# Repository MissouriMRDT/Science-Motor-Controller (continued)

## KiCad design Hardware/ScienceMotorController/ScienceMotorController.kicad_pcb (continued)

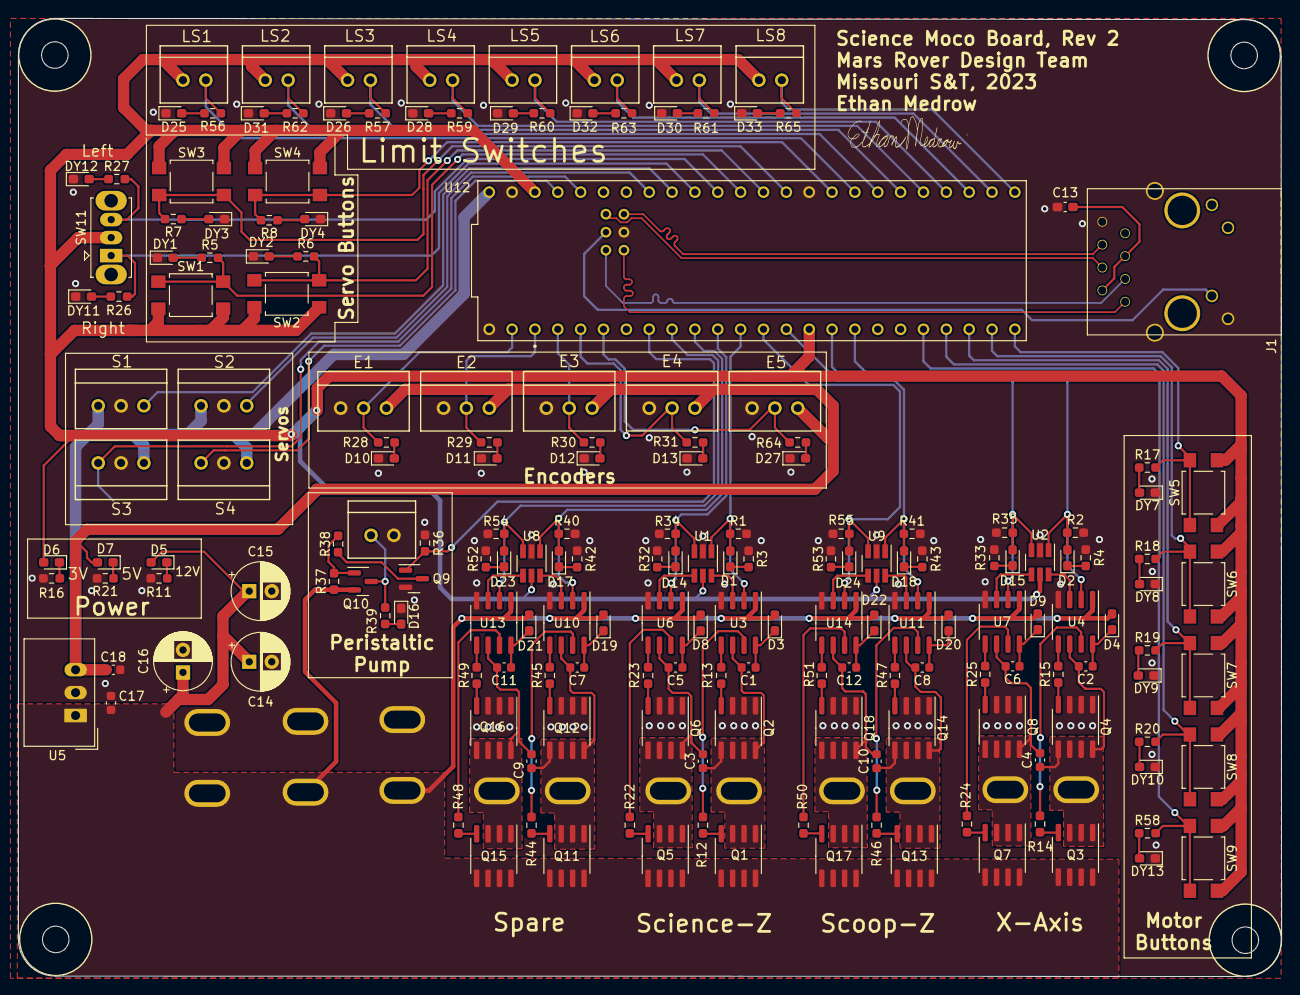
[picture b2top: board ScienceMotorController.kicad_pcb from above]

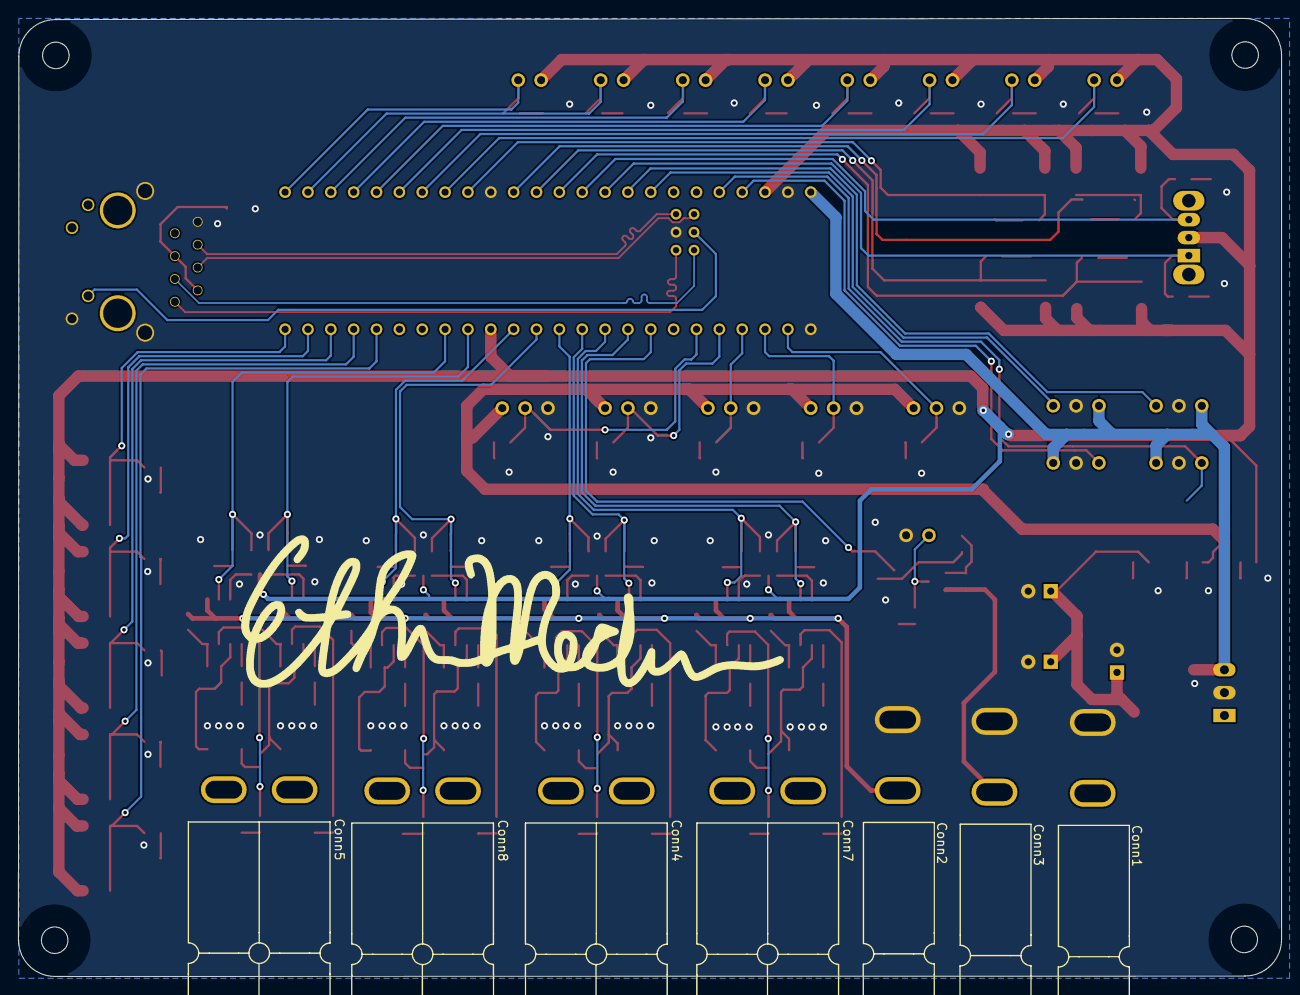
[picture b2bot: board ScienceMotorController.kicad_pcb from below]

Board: 2 copper layers, 140.4 x 106.5 mm, 197 parts (7 on the bottom side), 142 nets.

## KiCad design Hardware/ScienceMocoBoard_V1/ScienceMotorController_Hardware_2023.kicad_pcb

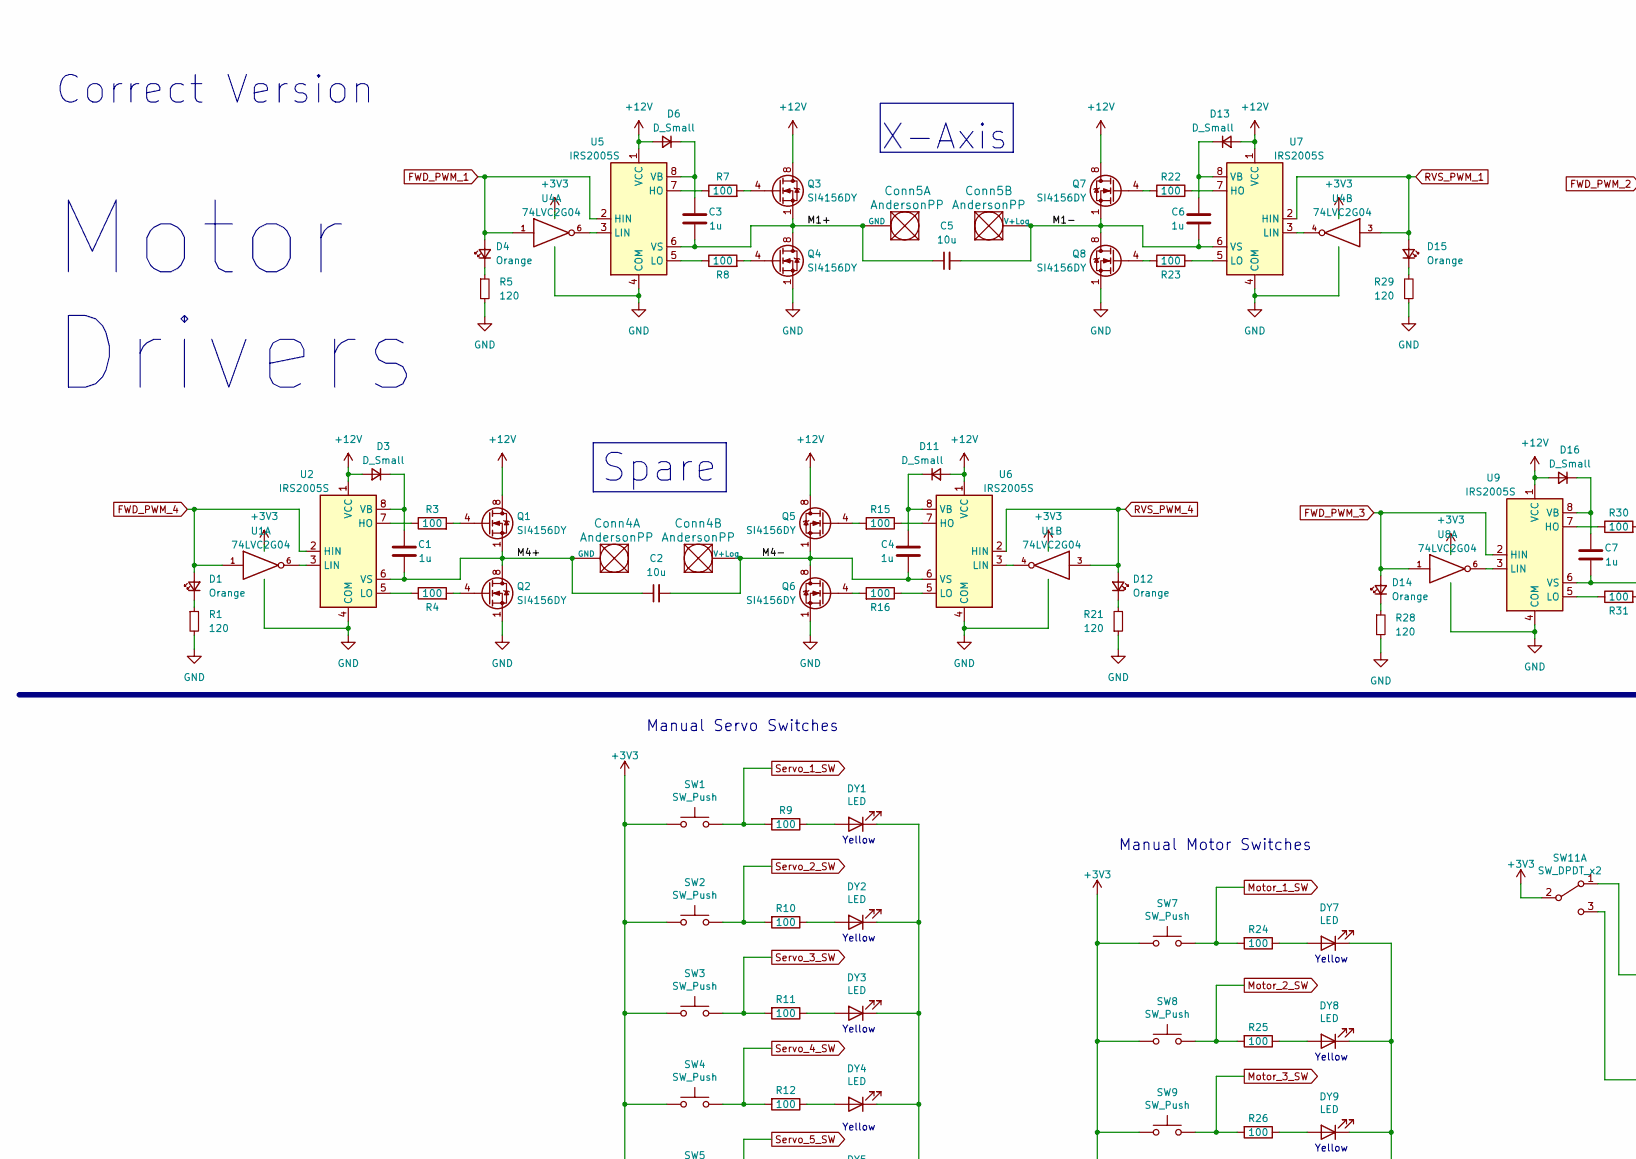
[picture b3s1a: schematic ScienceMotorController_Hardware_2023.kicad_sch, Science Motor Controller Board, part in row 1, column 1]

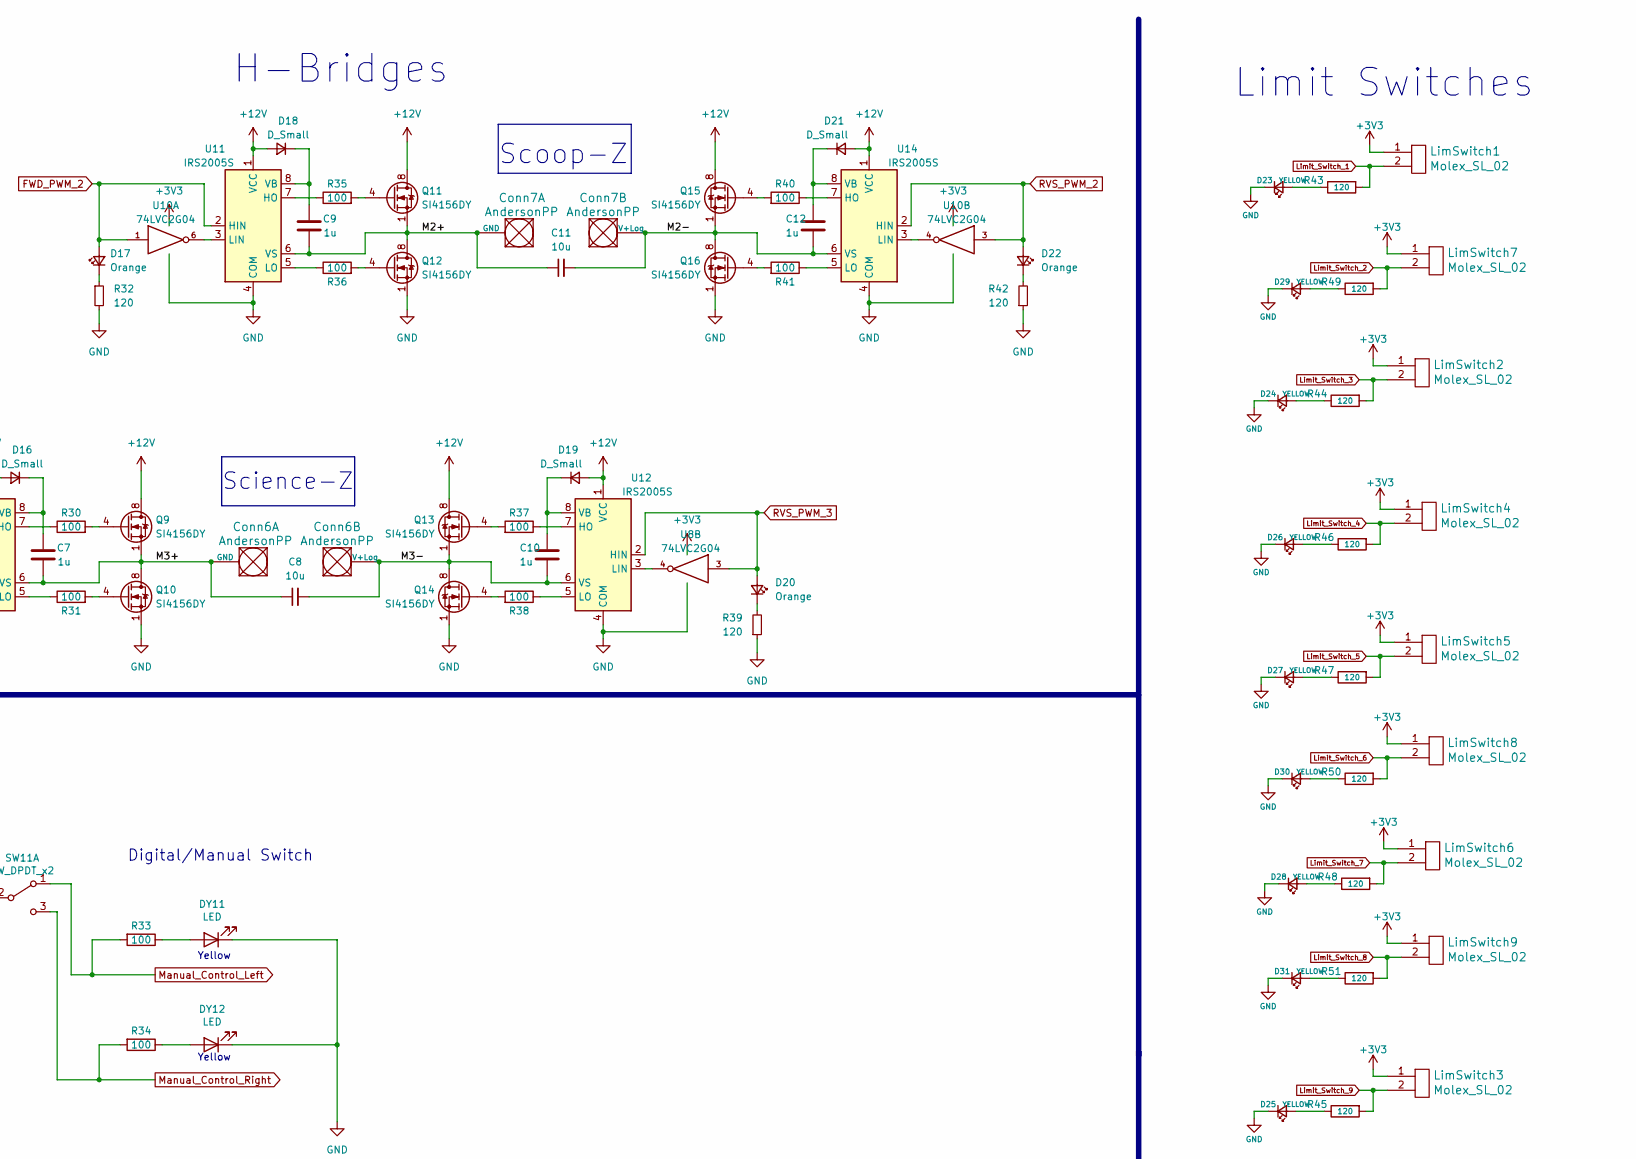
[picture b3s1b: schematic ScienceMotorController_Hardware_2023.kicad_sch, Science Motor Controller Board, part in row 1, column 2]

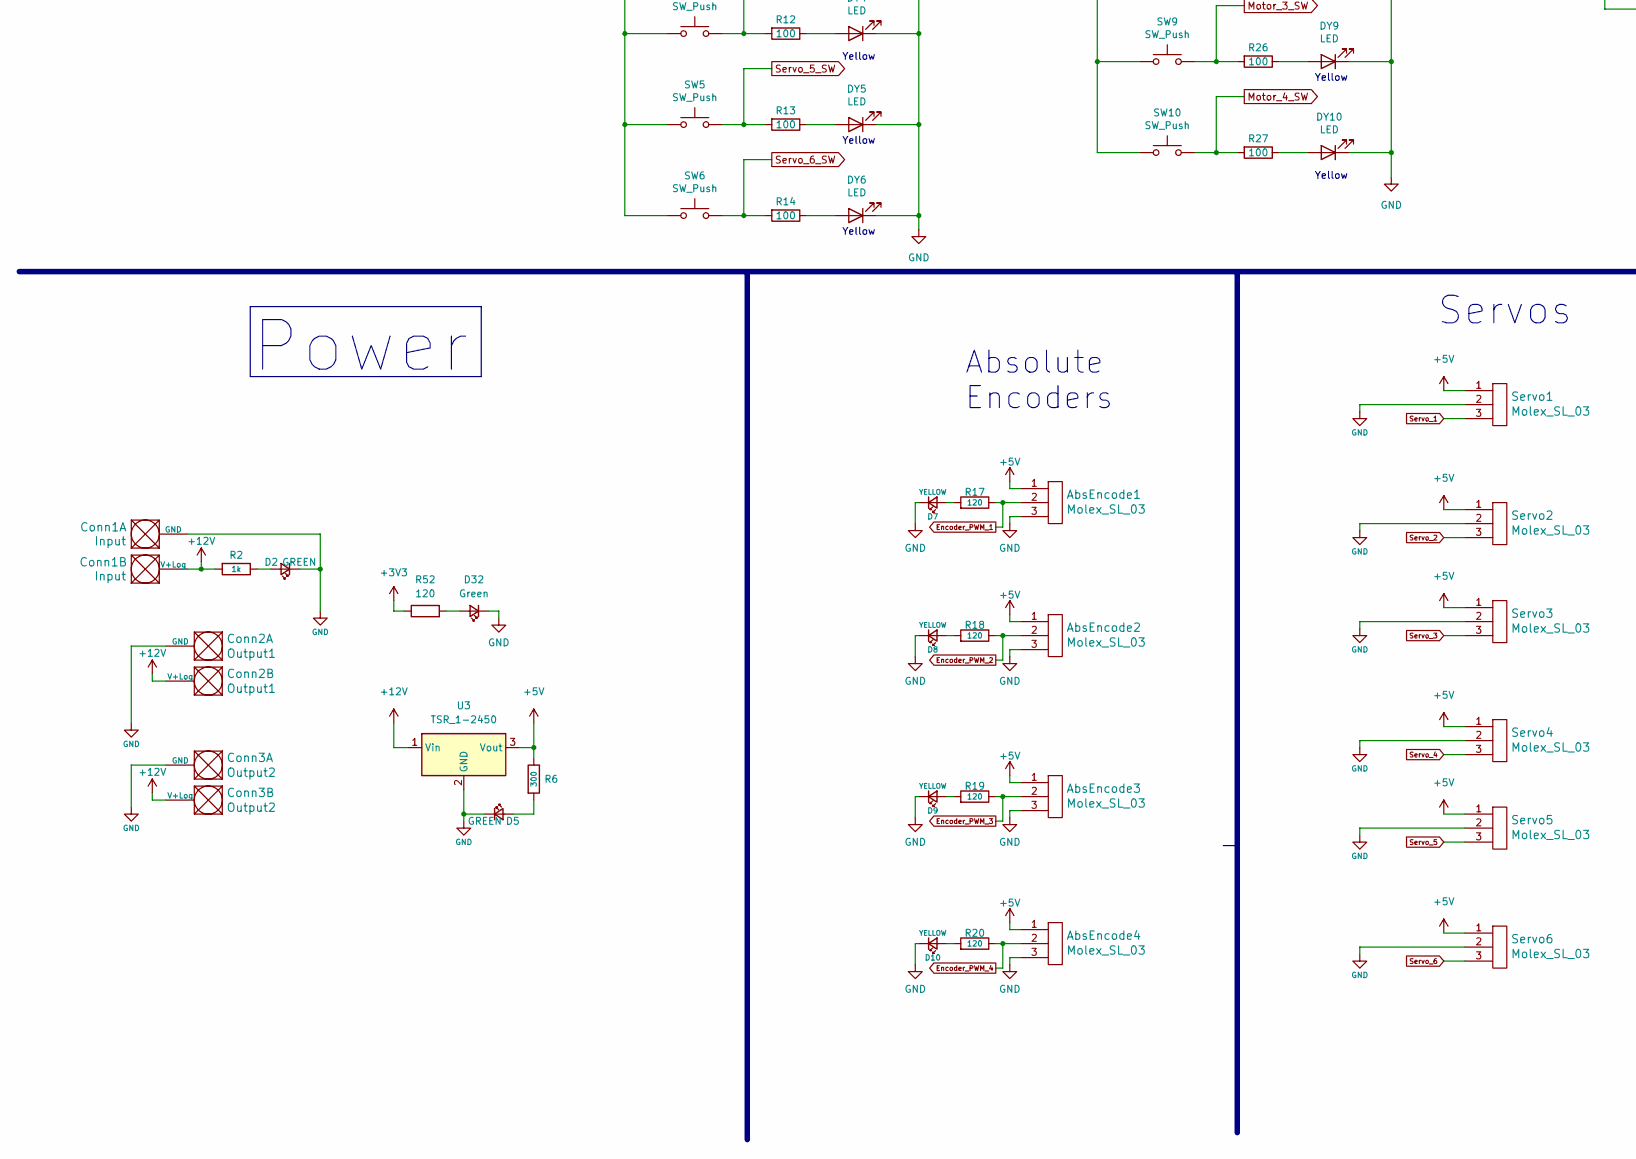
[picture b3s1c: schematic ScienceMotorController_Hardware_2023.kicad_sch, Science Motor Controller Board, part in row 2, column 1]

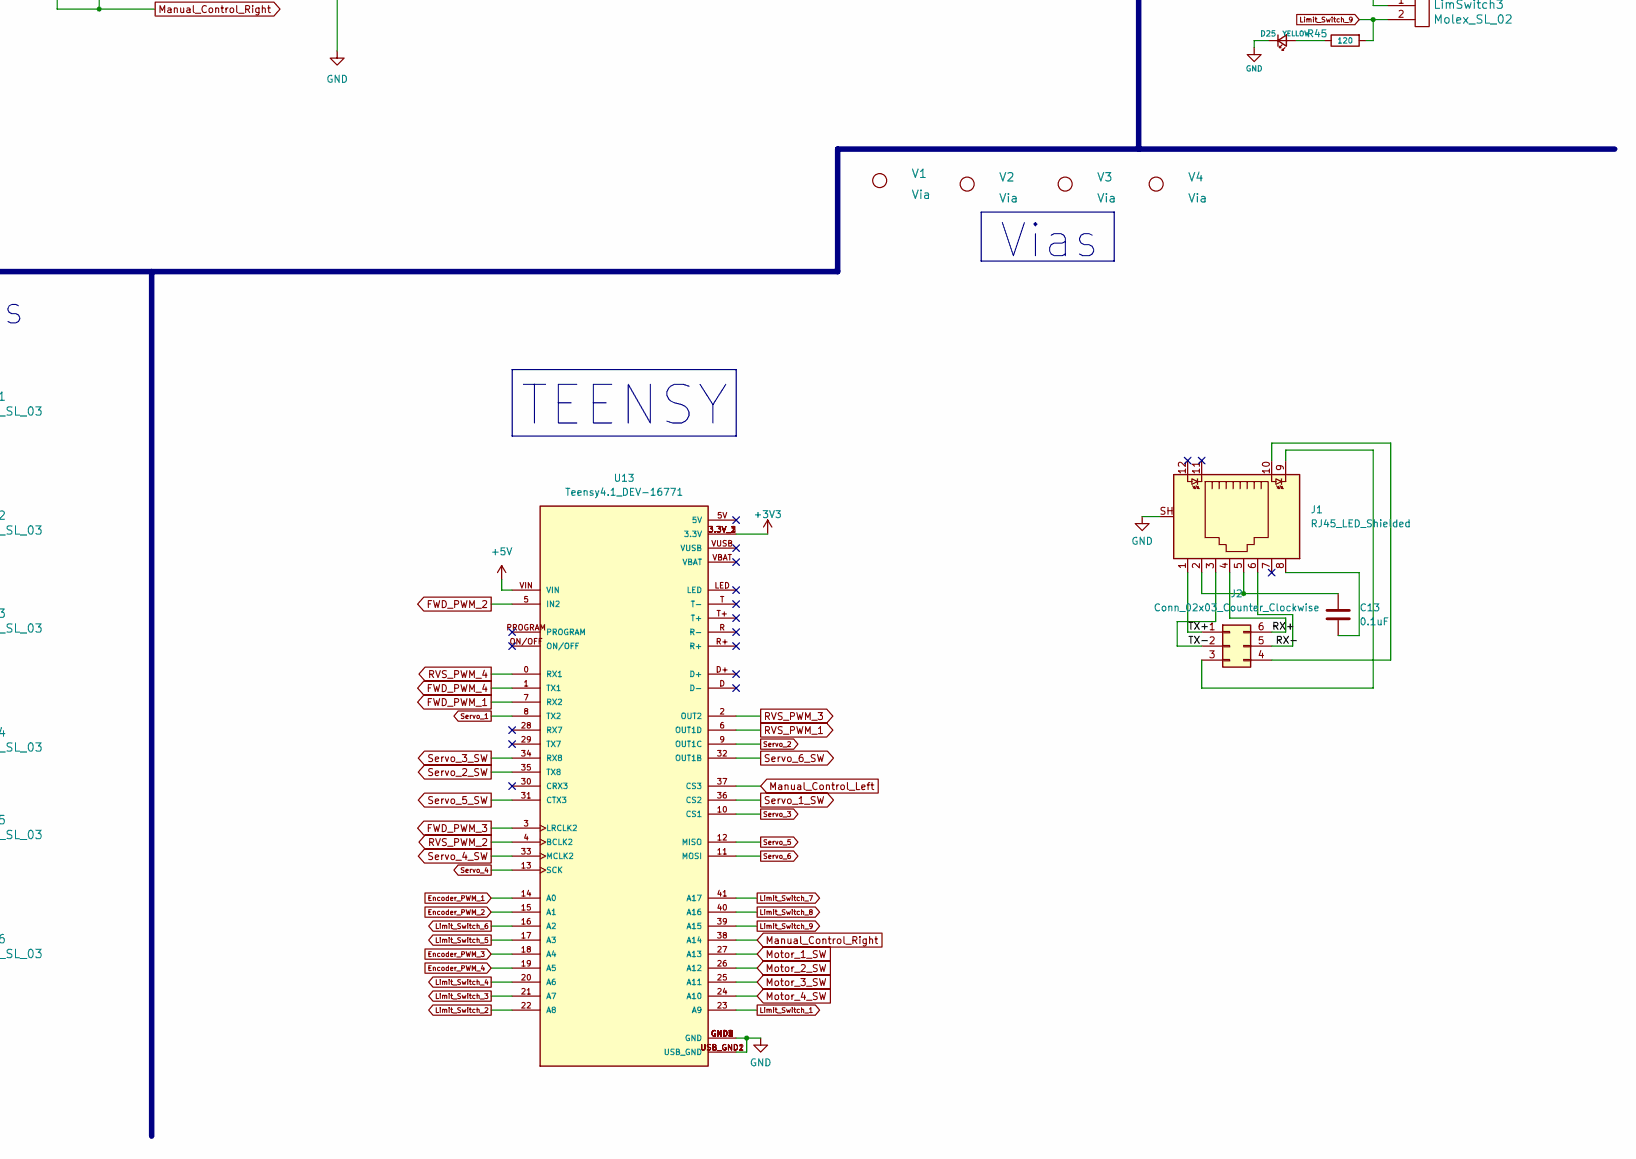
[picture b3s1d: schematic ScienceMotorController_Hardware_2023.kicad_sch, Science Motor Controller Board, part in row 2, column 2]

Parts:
AbsEncode1, AbsEncode2, AbsEncode3, AbsEncode4: Molex_SL_03; MOLEX_SL_03_Vertical
C1, C3, C4, C6, C7, C9, C10, C12: 1u; C_0603_1608Metric
C2, C5, C8, C11: 10u; C_0603_1608Metric
C13: 0.1uF; C_0603_1608Metric_Pad1.08x0.95mm_HandSolder
Conn1: Input; Square_Anderson_2_H_Side_By_Side
Conn2: Output1; Square_Anderson_2_H_Side_By_Side
Conn3: Output2; Square_Anderson_2_H_Side_By_Side
Conn4, Conn5, Conn6, Conn7: AndersonPP; Square_Anderson_2_H_Side_By_Side
D1, D4, D12, D14, D15, D17, D20, D22: Orange; LED_0603_1608Metric_Pad1.05x0.95mm_HandSolder
D2, D5: GREEN; LED_0603_1608Metric_Pad1.05x0.95mm_HandSolder
D3, D6, D11, D13, D16, D18, D19, D21: D_Small; LED_0603_1608Metric_Pad1.05x0.95mm_HandSolder
D7, D8, D9, D10, D23, D24, D25, D26, D27, D28, D29, D30, D31: YELLOW; LED_0603_1608Metric_Pad1.05x0.95mm_HandSolder
D32: Green; LED_0603_1608Metric_Pad1.05x0.95mm_HandSolder
DY1, DY2, DY3, DY4, DY5, DY6, DY7, DY8, DY9, DY10, DY11, DY12: LED; LED_0603_1608Metric_Pad1.05x0.95mm_HandSolder
J1: RJ45_LED_Shielded; RJ45_Teensy
J2: Conn_02x03_Counter_Clockwise; PinHeader_2x03_P2.00mm_Vertical
LimSwitch1, LimSwitch2, LimSwitch3, LimSwitch4, LimSwitch5, LimSwitch6, LimSwitch7, LimSwitch8, LimSwitch9: Molex_SL_02; MOLEX_SL_02_Vertical
Q1, Q2, Q3, Q4, Q5, Q6, Q7, Q8, Q9, Q10, Q11, Q12, Q13, Q14, Q15, Q16: SI4156DY; SOIC-8_3.9x4.9mm_P1.27mm
R1, R5, R17, R18, R19, R20, R21, R28, R29, R32, R39, R42, R43, R44, R45, R46, R47, R48, R49, R50, R51, R52: 120; R_0603_1608Metric_Pad0.98x0.95mm_HandSolder
R2: 1k; R_0603_1608Metric_Pad0.98x0.95mm_HandSolder
R3, R4, R7, R8, R9, R10, R11, R12, R13, R14, R15, R16, R22, R23, R24, R25, R26, R27, R30, R31, R33, R34, R35, R36, R37, R38, R40, R41: 100; R_0603_1608Metric_Pad0.98x0.95mm_HandSolder
R6: 300; R_0603_1608Metric_Pad0.98x0.95mm_HandSolder
SW1, SW2, SW3, SW4, SW5, SW6, SW7, SW8, SW9, SW10: SW_Push; SW_SPST_EVPBF
SW11: SW_DPDT_x2; SW_Slide_1P2T_CK_OS102011MS2Q
Servo1, Servo2, Servo3, Servo4, Servo5, Servo6: Molex_SL_03; MOLEX_SL_03_Vertical
U1, U4, U8, U10: 74LVC2G04; SOT-23-6_Handsoldering
U2, U5, U6, U7, U9, U11, U12, U14: IRS2005S; SOIC-8_3.9x4.9mm_P1.27mm
U3: TSR_1-2450; Converter_DCDC_TRACO_TSR-1_THT
U13: Teensy4.1_DEV-16771; Teensy_4_1_Bare; PARTREV 4.1
V1, V2, V3, V4: Via; 4_40_Hole_Corner

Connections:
+3V3: LimSwitch1.1, LimSwitch2.1, LimSwitch3.1, LimSwitch4.1, LimSwitch5.1, LimSwitch6.1, LimSwitch7.1, LimSwitch8.1, LimSwitch9.1, R52.1, SW1.2, SW2.1, SW3.1, SW4.1, SW5.1, SW6.1, SW7.2, SW8.1, SW9.1, SW10.1, SW11.2 (B), U1.5 (VCC), U4.5 (VCC), U8.5 (VCC), U10.5 (VCC), U13.3.3V_1 (3.3V), U13.3.3V_2 (3.3V), U13.3.3V_3 (3.3V)
+5V: AbsEncode1.1, AbsEncode2.1, AbsEncode3.1, AbsEncode4.1, R6.1, Servo1.1, Servo2.1, Servo3.1, Servo4.1, Servo5.1, Servo6.1, U3.3 (Vout), U13.VIN
+12V: Conn1.2 (V+Log), Conn2.2 (V+Log), Conn3.2 (V+Log), D3.2 (A), D6.2 (A), D11.2 (A), D13.2 (A), D16.2 (A), D18.2 (A), D19.2 (A), D21.2 (A), Q1.5 (D), Q1.6 (D), Q1.7 (D), Q1.8 (D), Q3.5 (D), Q3.6 (D), Q3.7 (D), Q3.8 (D), Q5.5 (D), Q5.6 (D), Q5.7 (D), Q5.8 (D), Q7.5 (D), Q7.6 (D), Q7.7 (D), Q7.8 (D), Q9.5 (D), Q9.6 (D), Q9.7 (D), Q9.8 (D), Q11.5 (D), Q11.6 (D), Q11.7 (D), Q11.8 (D), Q13.5 (D), Q13.6 (D), Q13.7 (D), Q13.8 (D), Q15.5 (D), Q15.6 (D), Q15.7 (D), Q15.8 (D), R2.2, U2.1 (VCC), U3.1 (Vin), U5.1 (VCC), U6.1 (VCC), U7.1 (VCC), U9.1 (VCC), U11.1 (VCC), U12.1 (VCC), U14.1 (VCC)
/M1+: C3.2, C5.1, Conn5.1 (GND), Q3.1 (S), Q3.2 (S), Q3.3 (S), Q4.5 (D), Q4.6 (D), Q4.7 (D), Q4.8 (D), U5.6 (VS)
/M1-: C5.2, C6.2, Conn5.2 (V+Log), Q7.1 (S), Q7.2 (S), Q7.3 (S), Q8.5 (D), Q8.6 (D), Q8.7 (D), Q8.8 (D), U7.6 (VS)
/M2+: C9.2, C11.1, Conn7.1 (GND), Q11.1 (S), Q11.2 (S), Q11.3 (S), Q12.5 (D), Q12.6 (D), Q12.7 (D), Q12.8 (D), U11.6 (VS)
/M2-: C11.2, C12.2, Conn7.2 (V+Log), Q15.1 (S), Q15.2 (S), Q15.3 (S), Q16.5 (D), Q16.6 (D), Q16.7 (D), Q16.8 (D), U14.6 (VS)
/M3+: C7.2, C8.1, Conn6.1 (GND), Q9.1 (S), Q9.2 (S), Q9.3 (S), Q10.5 (D), Q10.6 (D), Q10.7 (D), Q10.8 (D), U9.6 (VS)
/M3-: C8.2, C10.2, Conn6.2 (V+Log), Q13.1 (S), Q13.2 (S), Q13.3 (S), Q14.5 (D), Q14.6 (D), Q14.7 (D), Q14.8 (D), U12.6 (VS)
/M4+: C1.2, C2.1, Conn4.1 (GND), Q1.1 (S), Q1.2 (S), Q1.3 (S), Q2.5 (D), Q2.6 (D), Q2.7 (D), Q2.8 (D), U2.6 (VS)
/M4-: C2.2, C4.2, Conn4.2 (V+Log), Q5.1 (S), Q5.2 (S), Q5.3 (S), Q6.5 (D), Q6.6 (D), Q6.7 (D), Q6.8 (D), U6.6 (VS)
/RX+: J1.4, J2.6
/RX-: J1.6, J2.5
/TX+: J1.1, J2.1
/TX-: J1.3, J2.2
Encoder_PWM_1: AbsEncode1.2, R17.1, U13.14 (A0)
Encoder_PWM_2: AbsEncode2.2, R18.1, U13.15 (A1)
Encoder_PWM_3: AbsEncode3.2, R19.1, U13.18 (A4)
Encoder_PWM_4: AbsEncode4.2, R20.1, U13.19 (A5)
FWD_PWM_1: D4.2 (A), U4.1, U5.2 (HIN), U13.7 (RX2)
FWD_PWM_2: D17.2 (A), U10.1, U11.2 (HIN), U13.5 (IN2)
FWD_PWM_3: D14.2 (A), U8.1, U9.2 (HIN), U13.3 (LRCLK2)
FWD_PWM_4: D1.2 (A), U1.1, U2.2 (HIN), U13.1 (TX1)
GND: AbsEncode1.3, AbsEncode2.3, AbsEncode3.3, AbsEncode4.3, Conn1.1 (GND), Conn2.1 (GND), Conn3.1 (GND), D2.1 (K), D5.1 (K), D7.1 (K), D8.1 (K), D9.1 (K), D10.1 (K), D23.1 (K), D24.1 (K), D25.1 (K), D26.1 (K), D27.1 (K), D28.1 (K), D29.1 (K), D30.1 (K), D31.1 (K), D32.1 (K), DY1.1 (K), DY2.1 (K), DY3.1 (K), DY4.1 (K), DY5.1 (K), DY6.1 (K), DY7.1 (K), DY8.1 (K), DY9.1 (K), DY10.1 (K), DY11.1 (K), DY12.1 (K), J1.SH, Q2.1 (S), Q2.2 (S), Q2.3 (S), Q4.1 (S), Q4.2 (S), Q4.3 (S), Q6.1 (S), Q6.2 (S), Q6.3 (S), Q8.1 (S), Q8.2 (S), Q8.3 (S), Q10.1 (S), Q10.2 (S), Q10.3 (S), Q12.1 (S), Q12.2 (S), Q12.3 (S), Q14.1 (S), Q14.2 (S), Q14.3 (S), Q16.1 (S), Q16.2 (S), Q16.3 (S), R1.2, R5.2, R21.1, R28.2, R29.1, R32.2, R39.1, R42.1, Servo1.2, Servo2.2, Servo3.2, Servo4.2, Servo5.2, Servo6.2, U1.2 (GND), U2.4 (COM), U3.2 (GND), U4.2 (GND), U5.4 (COM), U6.4 (COM), U7.4 (COM), U8.2 (GND), U9.4 (COM), U10.2 (GND), U11.4 (COM), U12.4 (COM), U13.GND1 (GND), U13.GND2 (GND), U13.GND3 (GND), U13.GND4 (GND), U13.GND5 (GND), U13.USB_GND1 (USB_GND), U13.USB_GND2 (USB_GND), U14.4 (COM)
Limit_Switch_1: LimSwitch1.2, R43.2, U13.23 (A9)
Limit_Switch_2: LimSwitch7.2, R49.2, U13.22 (A8)
Limit_Switch_3: LimSwitch2.2, R44.2, U13.21 (A7)
Limit_Switch_4: LimSwitch4.2, R46.2, U13.20 (A6)
Limit_Switch_5: LimSwitch5.2, R47.2, U13.17 (A3)
Limit_Switch_6: LimSwitch8.2, R50.2, U13.16 (A2)
Limit_Switch_7: LimSwitch6.2, R48.2, U13.41 (A17)
Limit_Switch_8: LimSwitch9.2, R51.2, U13.40 (A16)
Limit_Switch_9: LimSwitch3.2, R45.2, U13.39 (A15)
Manual_Control_Left: R33.2, SW11.1 (A), U13.37 (CS3)
Manual_Control_Right: R34.2, SW11.3 (C), U13.38 (A14)
Motor_1_SW: R24.2, SW7.1, U13.27 (A13)
Motor_2_SW: R25.2, SW8.2, U13.26 (A12)
Motor_3_SW: R26.2, SW9.2, U13.25 (A11)
Motor_4_SW: R27.2, SW10.2, U13.24 (A10)
unnamed: C1.1, D3.1 (K), U2.8 (VB)
unnamed: C3.1, D6.1 (K), U5.8 (VB)
unnamed: C4.1, D11.1 (K), U6.8 (VB)
unnamed: C6.1, D13.1 (K), U7.8 (VB)
unnamed: C7.1, D16.1 (K), U9.8 (VB)
unnamed: C9.1, D18.1 (K), U11.8 (VB)
unnamed: C10.1, D19.1 (K), U12.8 (VB)
unnamed: C12.1, D21.1 (K), U14.8 (VB)
unnamed: C13.1, J1.2, J1.5
unnamed: C13.2, J1.8
unnamed: D1.1 (K), R1.1
unnamed: D2.2 (A), R2.1
unnamed: D4.1 (K), R5.1
unnamed: D5.2 (A), R6.2
unnamed: D7.2 (A), R17.2
unnamed: D8.2 (A), R18.2
unnamed: D9.2 (A), R19.2
unnamed: D10.2 (A), R20.2
unnamed: D12.1 (K), R21.2
unnamed: D14.1 (K), R28.1
unnamed: D15.1 (K), R29.2
unnamed: D17.1 (K), R32.1
unnamed: D20.1 (K), R39.2
unnamed: D22.1 (K), R42.2
unnamed: D23.2 (A), R43.1
unnamed: D24.2 (A), R44.1
unnamed: D25.2 (A), R45.1
unnamed: D26.2 (A), R46.1
unnamed: D27.2 (A), R47.1
unnamed: D28.2 (A), R48.1
unnamed: D29.2 (A), R49.1
unnamed: D30.2 (A), R50.1
unnamed: D31.2 (A), R51.1
unnamed: D32.2 (A), R52.2
unnamed: DY1.2 (A), R9.1
unnamed: DY2.2 (A), R10.1
unnamed: DY3.2 (A), R11.1
unnamed: DY4.2 (A), R12.1
unnamed: DY5.2 (A), R13.1
unnamed: DY6.2 (A), R14.1
unnamed: DY7.2 (A), R24.1
unnamed: DY8.2 (A), R25.1
unnamed: DY9.2 (A), R26.1
unnamed: DY10.2 (A), R27.1
unnamed: DY11.2 (A), R33.1
unnamed: DY12.2 (A), R34.1
unnamed: J1.9, J2.3
unnamed: J1.10, J2.4
unnamed: Q1.4 (G), R3.2
unnamed: Q2.4 (G), R4.2
unnamed: Q3.4 (G), R7.2
unnamed: Q4.4 (G), R8.2
unnamed: Q5.4 (G), R15.2
unnamed: Q6.4 (G), R16.2
unnamed: Q7.4 (G), R22.2
unnamed: Q8.4 (G), R23.2
unnamed: Q9.4 (G), R30.2
unnamed: Q10.4 (G), R31.2
unnamed: Q11.4 (G), R35.2
unnamed: Q12.4 (G), R36.2
unnamed: Q13.4 (G), R37.2
unnamed: Q14.4 (G), R38.2
unnamed: Q15.4 (G), R40.2
unnamed: Q16.4 (G), R41.2
unnamed: R3.1, U2.7 (HO)
unnamed: R4.1, U2.5 (LO)
unnamed: R7.1, U5.7 (HO)
unnamed: R8.1, U5.5 (LO)
unnamed: R15.1, U6.7 (HO)
unnamed: R16.1, U6.5 (LO)
unnamed: R22.1, U7.7 (HO)
unnamed: R23.1, U7.5 (LO)
unnamed: R30.1, U9.7 (HO)
unnamed: R31.1, U9.5 (LO)
unnamed: R35.1, U11.7 (HO)
unnamed: R36.1, U11.5 (LO)
unnamed: R37.1, U12.7 (HO)
unnamed: R38.1, U12.5 (LO)
unnamed: R40.1, U14.7 (HO)
unnamed: R41.1, U14.5 (LO)
unnamed: U1.4, U6.3 (LIN)
unnamed: U1.6, U2.3 (LIN)
unnamed: U4.4, U7.3 (LIN)
unnamed: U4.6, U5.3 (LIN)
unnamed: U8.6, U9.3 (LIN)
unnamed: U10.4, U14.3 (LIN)
unnamed: U10.6, U11.3 (LIN)
unnamed: U8.4, U12.3 (LIN)
RVS_PWM_1: D15.2 (A), U4.3, U7.2 (HIN), U13.6 (OUT1D)
RVS_PWM_2: D22.2 (A), U10.3, U13.4 (BCLK2), U14.2 (HIN)
RVS_PWM_3: D20.2 (A), U8.3, U12.2 (HIN), U13.2 (OUT2)
RVS_PWM_4: D12.2 (A), U1.3, U6.2 (HIN), U13.0 (RX1)
Servo_1: Servo1.3, U13.8 (TX2)
Servo_1_SW: R9.2, SW1.1, U13.36 (CS2)
Servo_2: Servo2.3, U13.9 (OUT1C)
Servo_2_SW: R10.2, SW2.2, U13.35 (TX8)
Servo_3: Servo3.3, U13.10 (CS1)
Servo_3_SW: R11.2, SW3.2, U13.34 (RX8)
Servo_4: Servo4.3, U13.13 (SCK)
Servo_4_SW: R12.2, SW4.2, U13.33 (MCLK2)
Servo_5: Servo5.3, U13.12 (MISO)
Servo_5_SW: R13.2, SW5.2, U13.31 (CTX3)
Servo_6: Servo6.3, U13.11 (MOSI)
Servo_6_SW: R14.2, SW6.2, U13.32 (OUT1B)

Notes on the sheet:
Yellow
TEENSY
X-Axis
Power
Absolute Encoders
Motor Drivers
Vias
Spare
Correct Version
Manual Servo Switches
Limit Switches
Servos
Science-Z
Manual Motor Switches
H-Bridges
Scoop-Z
Digital/Manual Switch

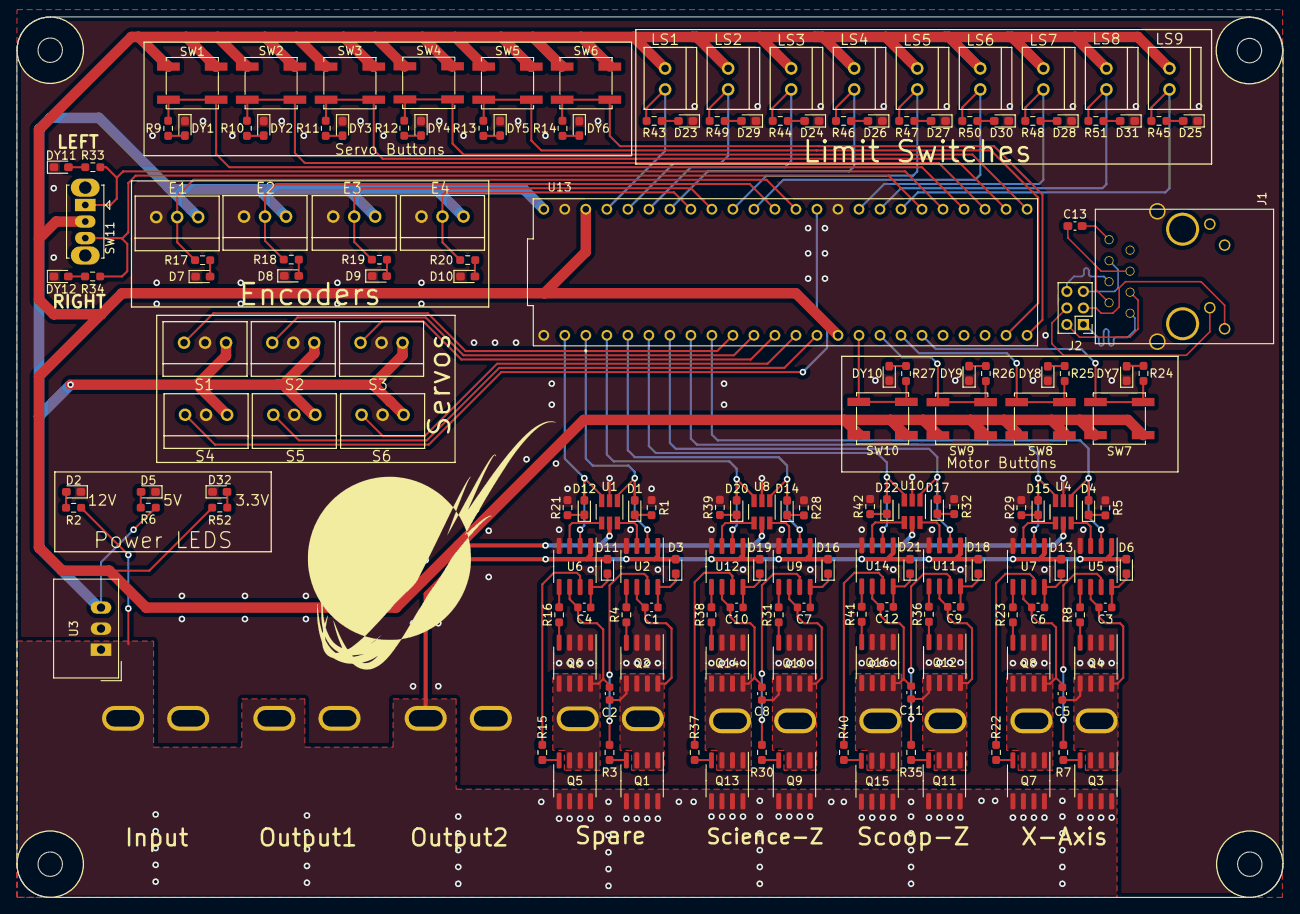
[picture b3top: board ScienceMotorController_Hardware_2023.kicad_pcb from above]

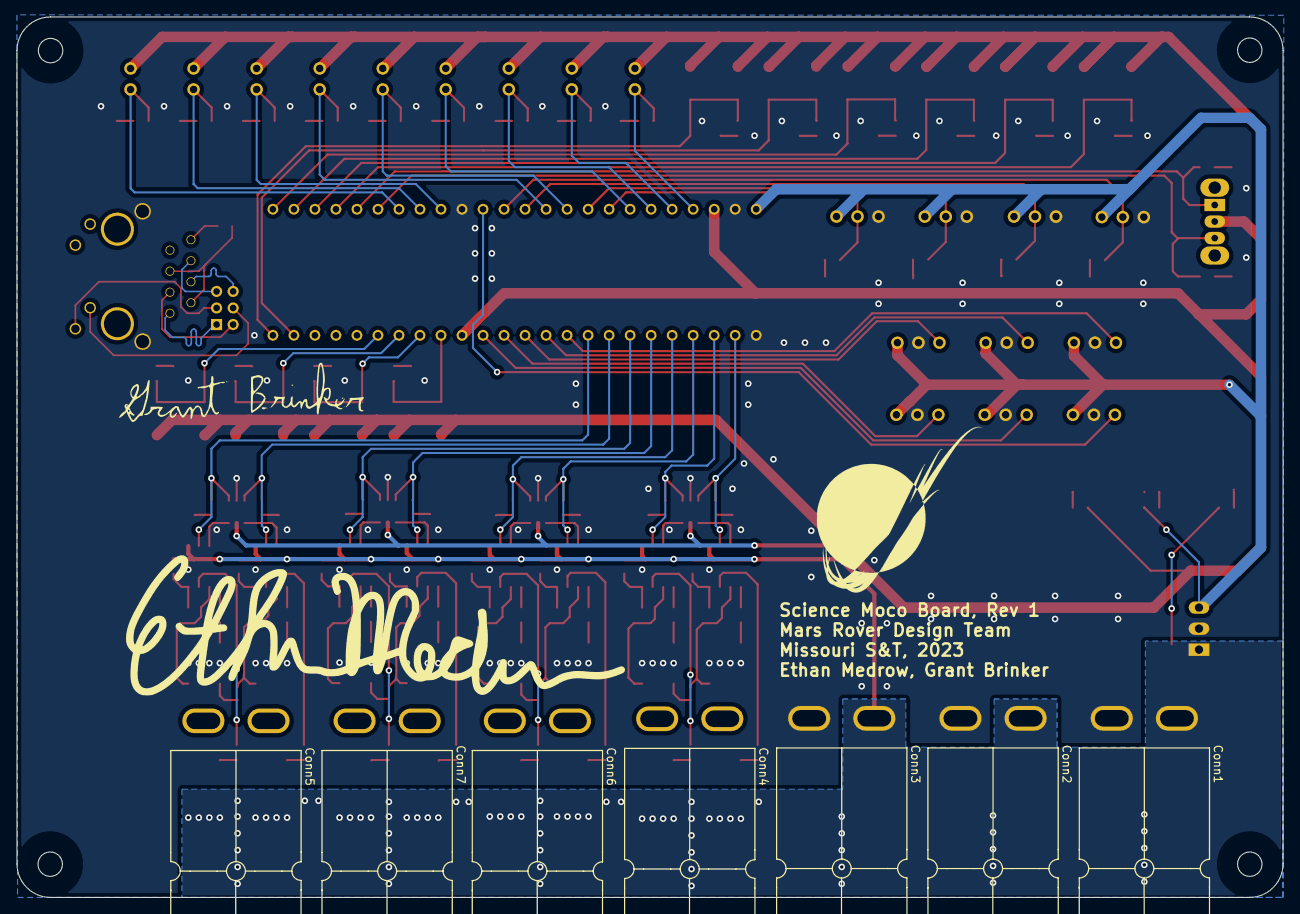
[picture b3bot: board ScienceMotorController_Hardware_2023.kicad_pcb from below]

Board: 2 copper layers, 153.0 x 106.4 mm, 182 parts (7 on the bottom side), 143 nets.
